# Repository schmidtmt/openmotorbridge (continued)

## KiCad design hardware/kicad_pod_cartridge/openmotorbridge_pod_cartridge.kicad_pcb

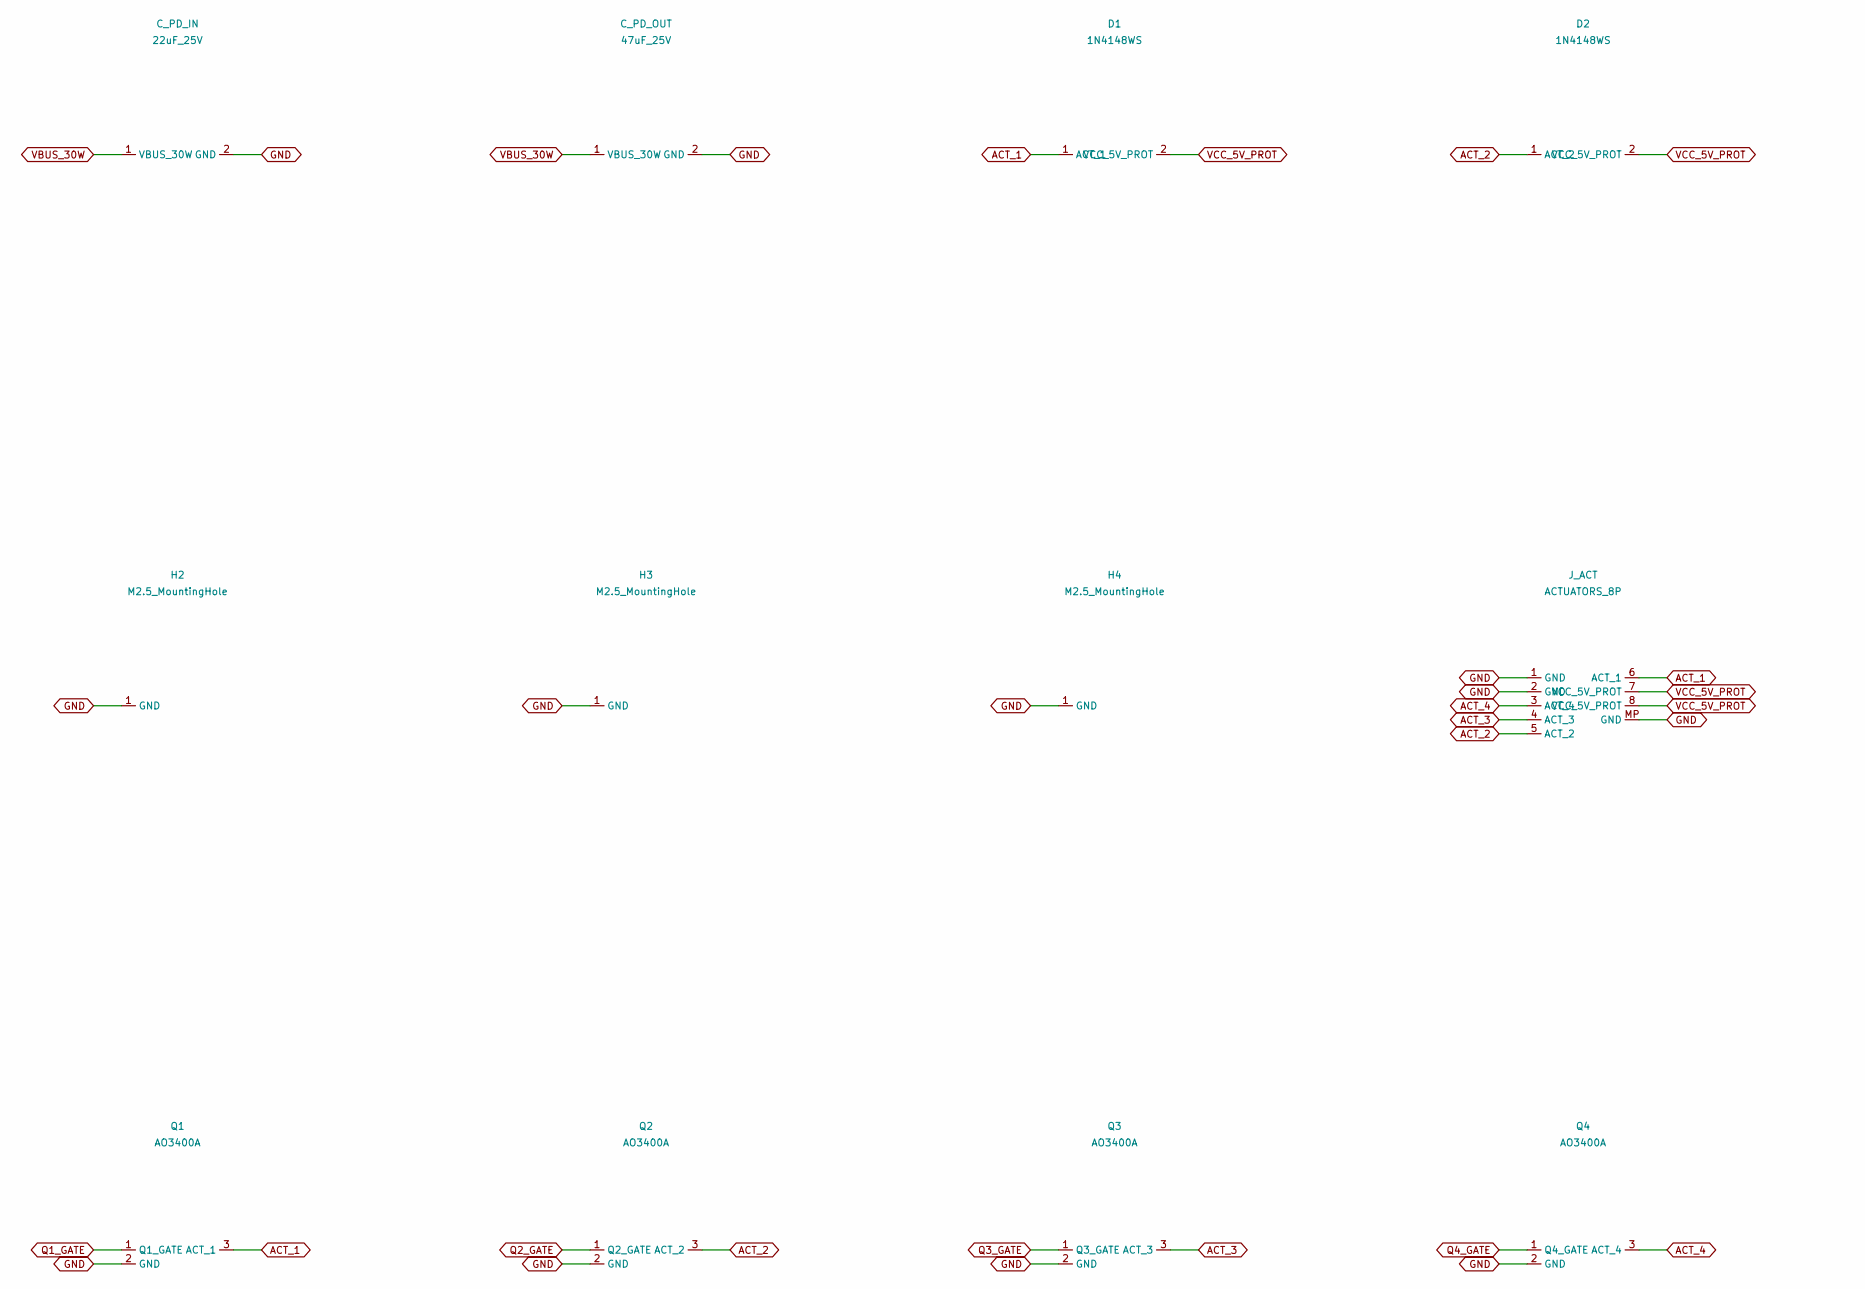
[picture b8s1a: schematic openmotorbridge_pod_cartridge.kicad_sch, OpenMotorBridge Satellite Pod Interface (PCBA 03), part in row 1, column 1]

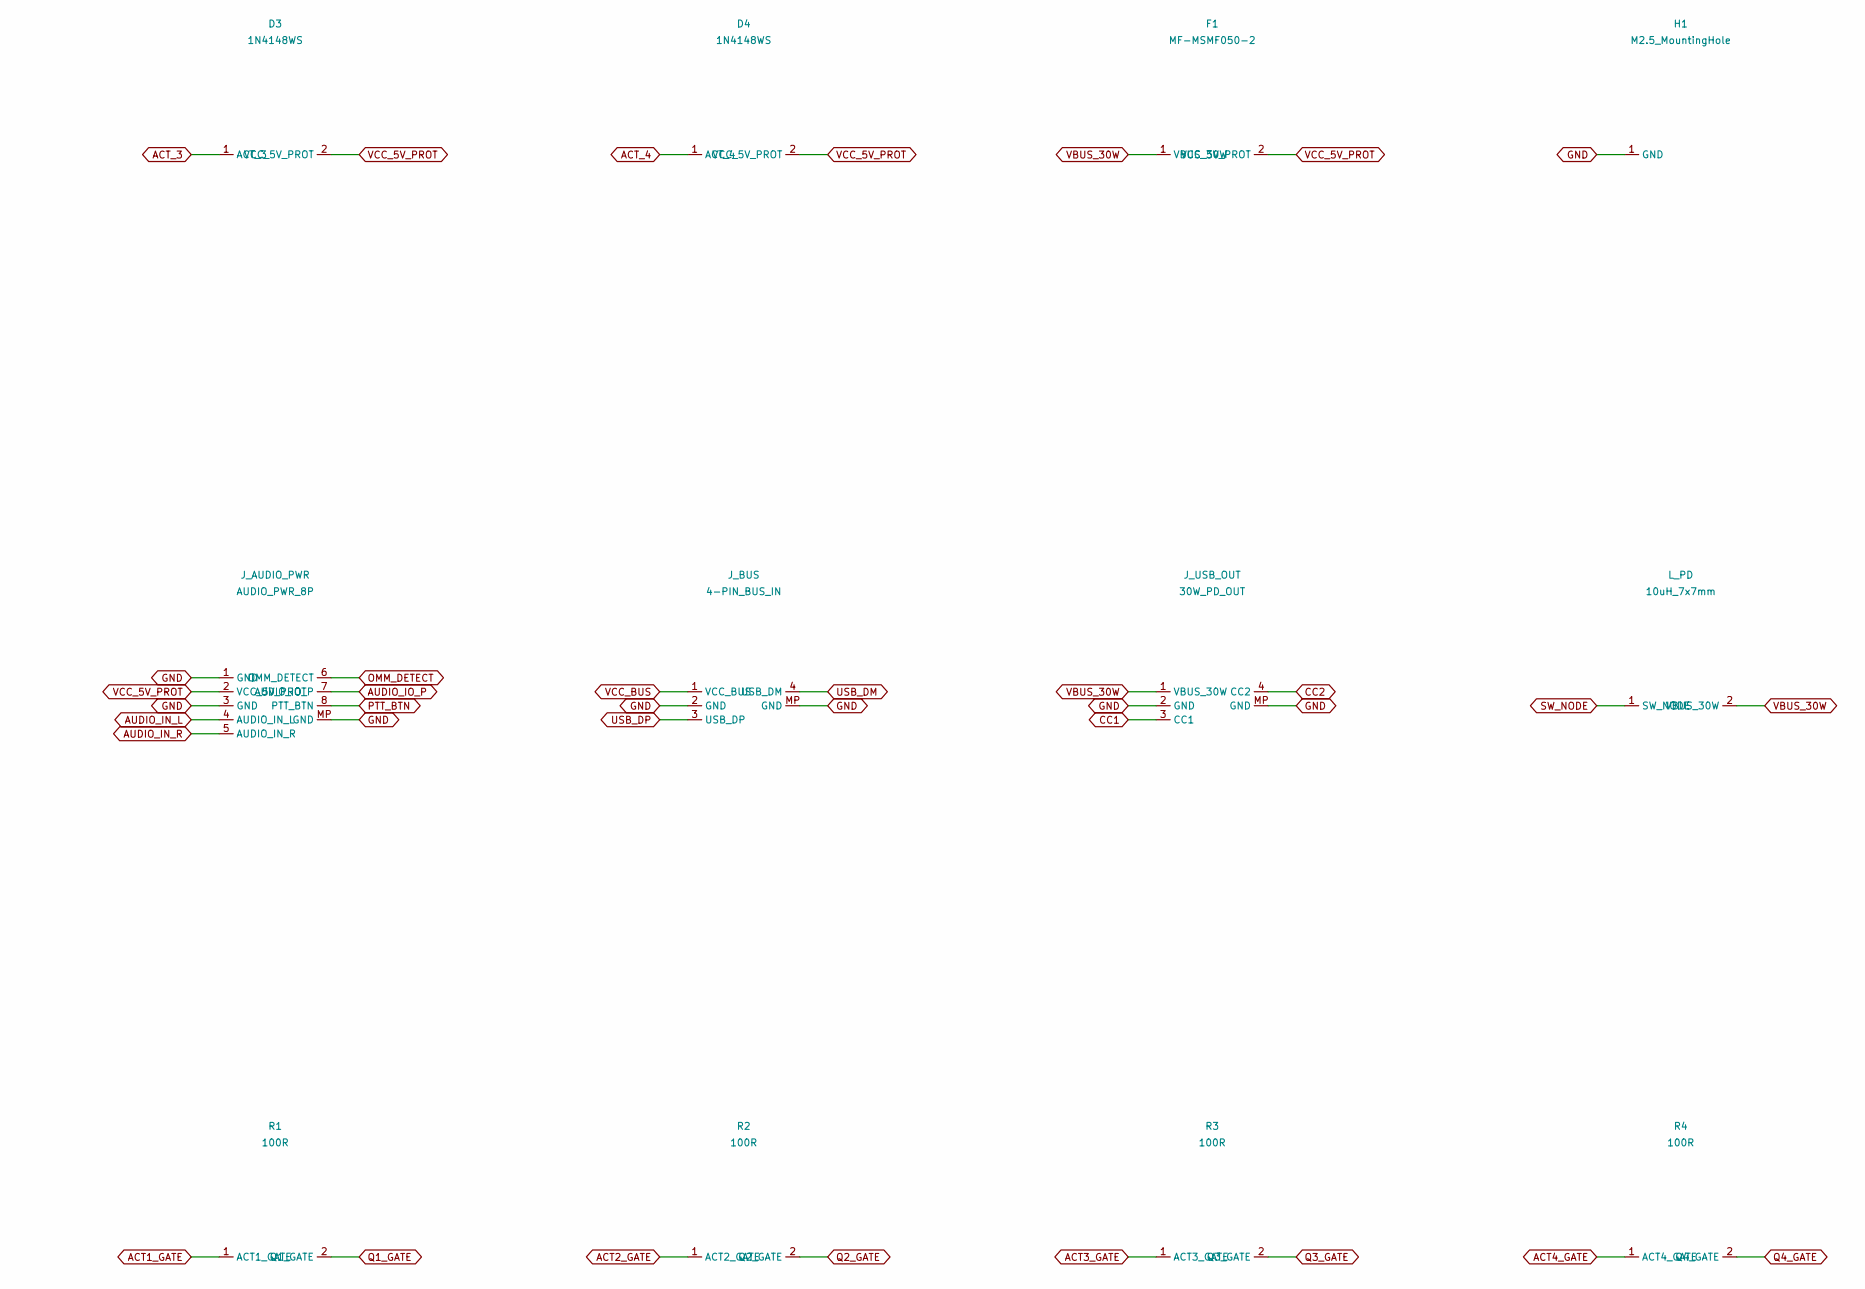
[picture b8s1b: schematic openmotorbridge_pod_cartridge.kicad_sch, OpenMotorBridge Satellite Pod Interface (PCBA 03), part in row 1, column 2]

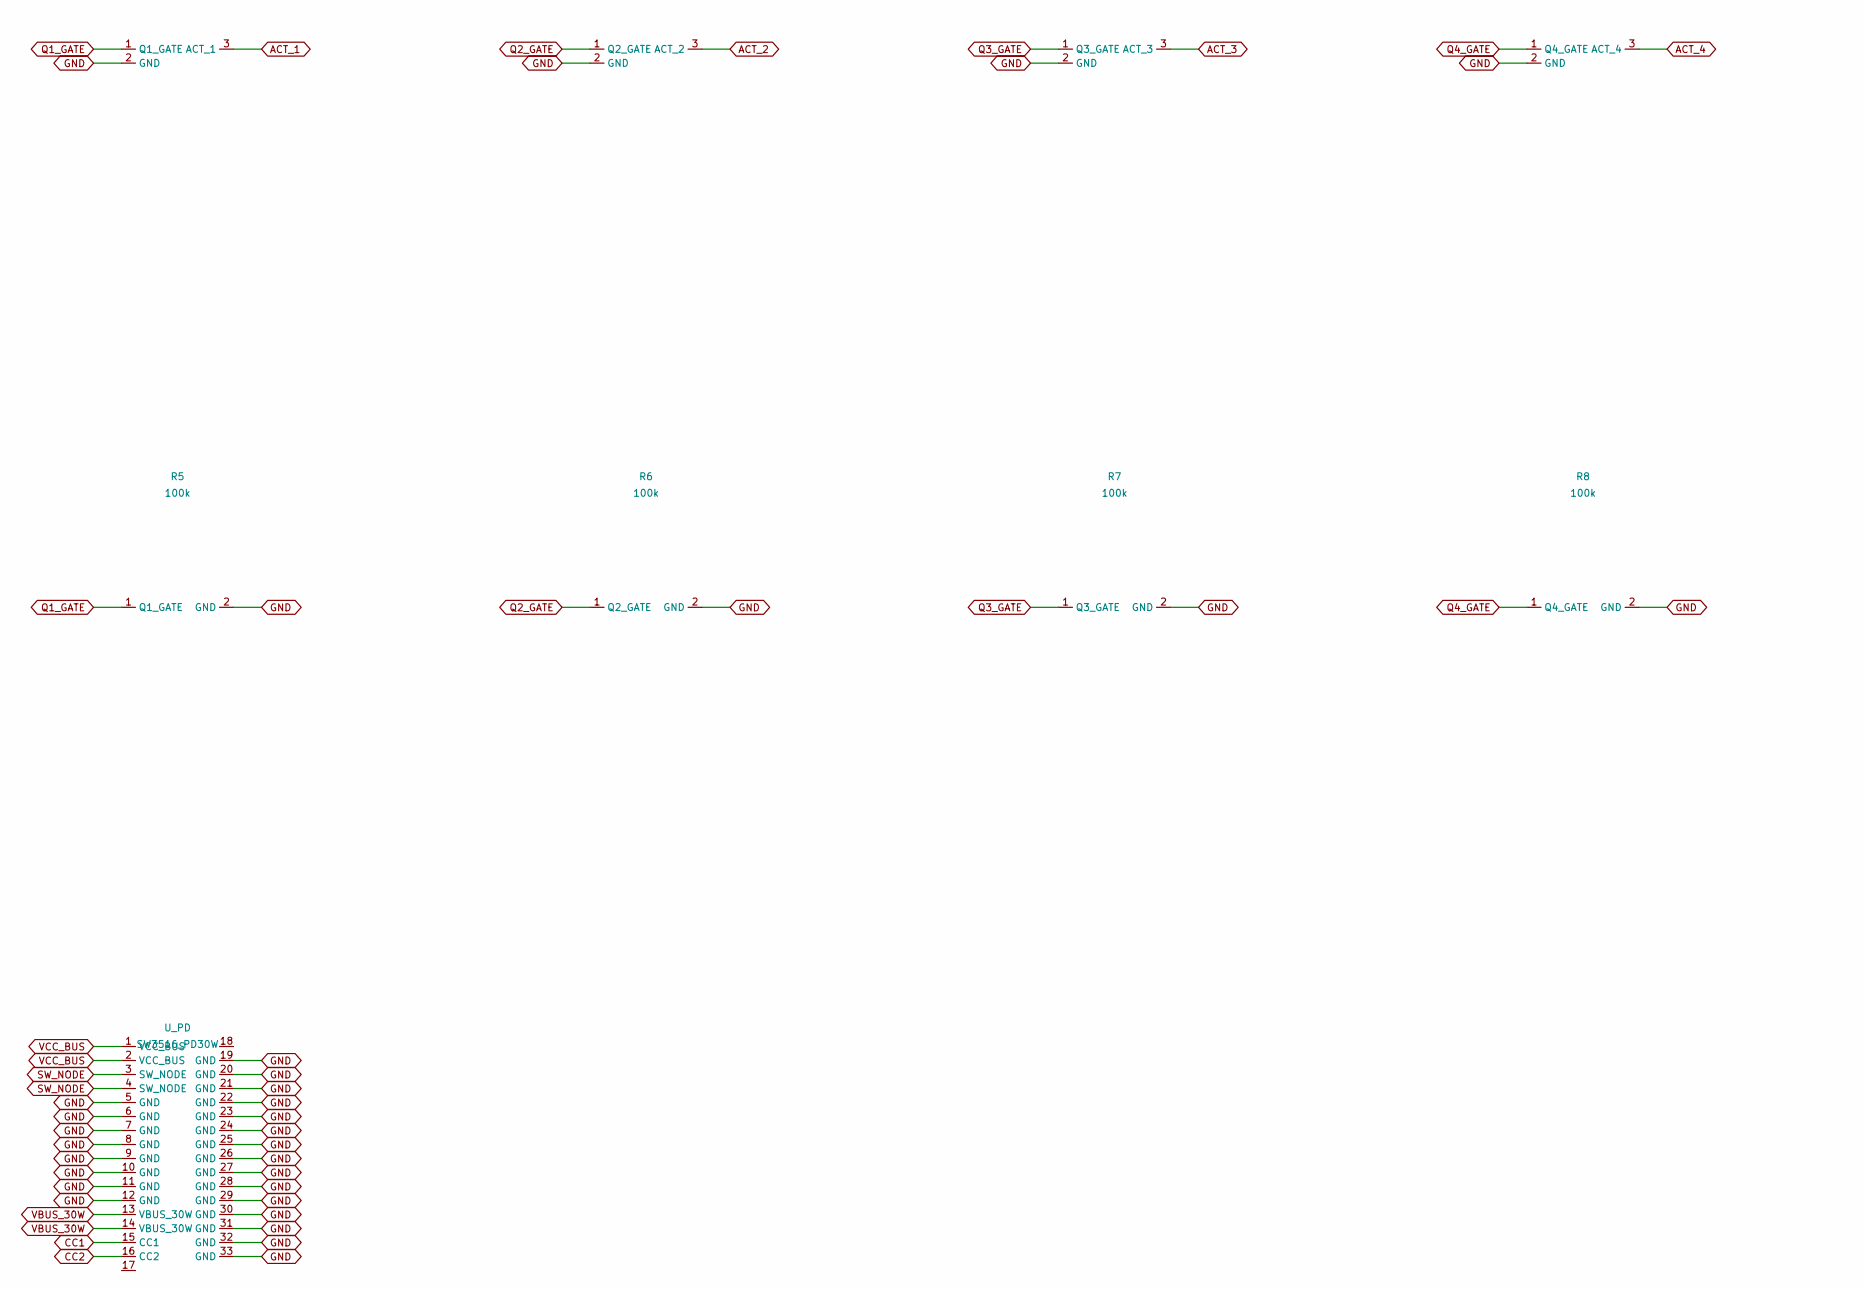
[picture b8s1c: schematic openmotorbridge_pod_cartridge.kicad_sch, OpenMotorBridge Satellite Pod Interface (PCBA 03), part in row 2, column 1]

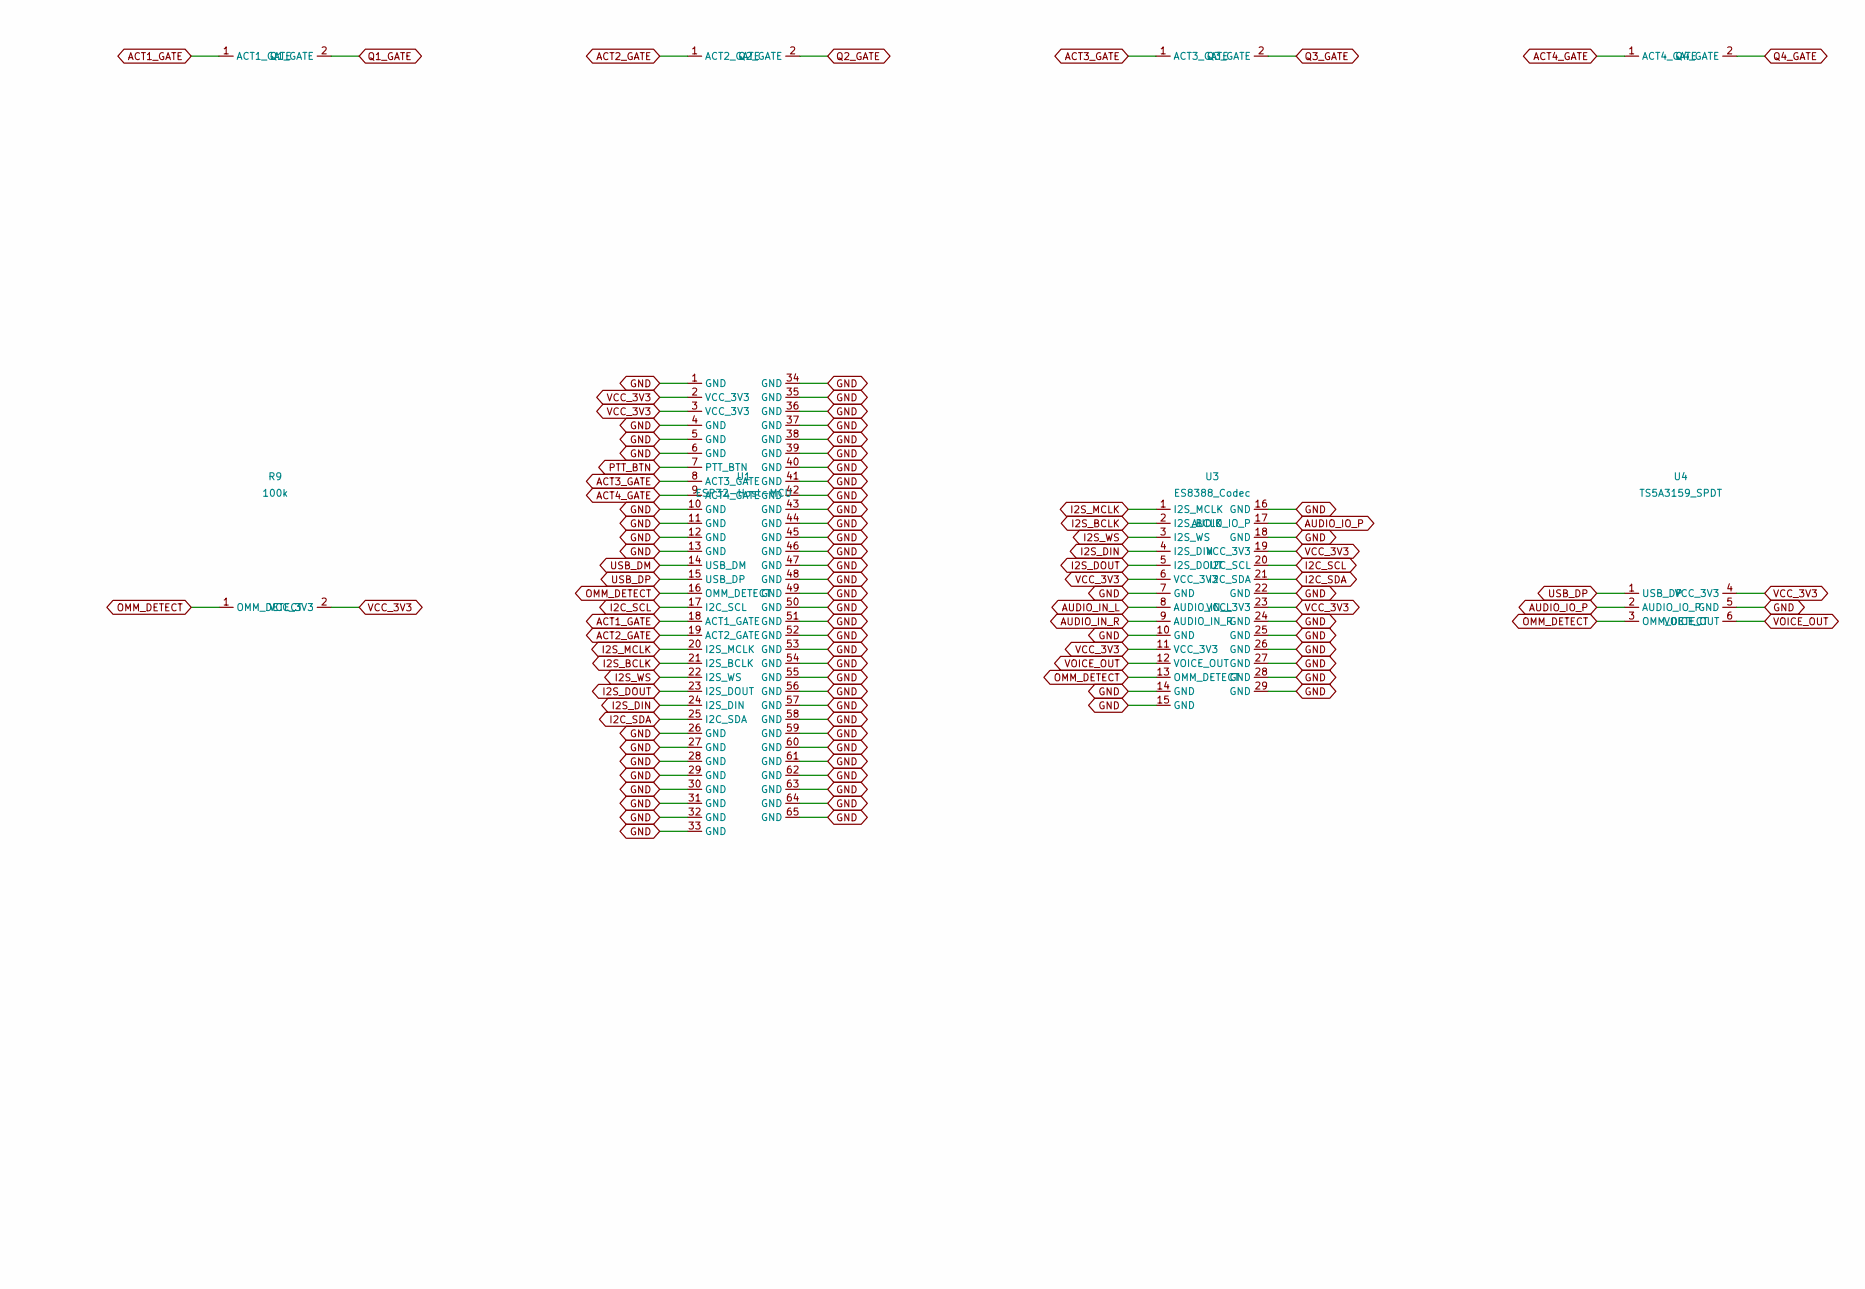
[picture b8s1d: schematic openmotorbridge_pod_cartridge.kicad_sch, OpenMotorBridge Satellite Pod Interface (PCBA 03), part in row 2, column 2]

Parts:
C_PD_IN: 22uF_25V; C_1210_3225Metric
C_PD_OUT: 47uF_25V; C_1210_3225Metric
D1, D2, D3, D4: 1N4148WS; D_SOD-323
F1: MF-MSMF050-2; Fuse_1812_4532Metric
H1, H2, H3, H4: M2.5_MountingHole; MountingHole_2.7mm_M2.5_Pad
J_ACT: ACTUATORS_8P; JST_SH_BM08B-SRSS-TB_1x08-1MP_P1.00mm_Vertical
J_AUDIO_PWR: AUDIO_PWR_8P; JST_SH_BM08B-SRSS-TB_1x08-1MP_P1.00mm_Vertical
J_BUS: 4-PIN_BUS_IN; JST_GH_BM04B-GHS-TBT_1x04-1MP_P1.25mm_Vertical
J_USB_OUT: 30W_PD_OUT; JST_GH_BM04B-GHS-TBT_1x04-1MP_P1.25mm_Vertical
L_PD: 10uH_7x7mm; L_Wuerth_WE-PD-Typ-7345
Q1, Q2, Q3, Q4: AO3400A; SOT-23
R1, R2, R3, R4: 100R; R_0603_1608Metric
R5, R6, R7, R8, R9: 100k; R_0603_1608Metric
U1: ESP32-Host-MCU; ESP32-C6-MINI-1
U3: ES8388_Codec; QFN-28-1EP_4x4mm_P0.4mm_EP2.4x2.4mm
U4: TS5A3159_SPDT; SOT-23-6
U_PD: SW3516_PD30W; QFN-32-1EP_5x5mm_P0.5mm_EP3.45x3.45mm_ThermalVias

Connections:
ACT1_GATE: R1.1 (ACT1_GATE), U1.18 (ACT1_GATE)
ACT2_GATE: R2.1 (ACT2_GATE), U1.19 (ACT2_GATE)
ACT3_GATE: R3.1 (ACT3_GATE), U1.8 (ACT3_GATE)
ACT4_GATE: R4.1 (ACT4_GATE), U1.9 (ACT4_GATE)
ACT_1: D1.1 (ACT_1), J_ACT.6 (ACT_1), Q1.3 (ACT_1)
ACT_2: D2.1 (ACT_2), J_ACT.5 (ACT_2), Q2.3 (ACT_2)
ACT_3: D3.1 (ACT_3), J_ACT.4 (ACT_3), Q3.3 (ACT_3)
ACT_4: D4.1 (ACT_4), J_ACT.3 (ACT_4), Q4.3 (ACT_4)
AUDIO_IN_L: J_AUDIO_PWR.4 (AUDIO_IN_L), U3.8 (AUDIO_IN_L)
AUDIO_IN_R: J_AUDIO_PWR.5 (AUDIO_IN_R), U3.9 (AUDIO_IN_R)
AUDIO_IO_P: J_AUDIO_PWR.7 (AUDIO_IO_P), U3.17 (AUDIO_IO_P), U4.2 (AUDIO_IO_P)
CC1: J_USB_OUT.3 (CC1), U_PD.15 (CC1)
CC2: J_USB_OUT.4 (CC2), U_PD.16 (CC2)
GND: C_PD_IN.2 (GND), C_PD_OUT.2 (GND), H1.1, H2.1, H3.1, H4.1, J_ACT.1 (GND), J_ACT.2 (GND), J_ACT.MP (GND), J_AUDIO_PWR.1 (GND), J_AUDIO_PWR.3 (GND), J_AUDIO_PWR.MP (GND), J_BUS.2 (GND), J_BUS.MP (GND), J_USB_OUT.2 (GND), J_USB_OUT.MP (GND), Q1.2 (GND), Q2.2 (GND), Q3.2 (GND), Q4.2 (GND), R5.2 (GND), R6.2 (GND), R7.2 (GND), R8.2 (GND), U1.1 (GND), U1.4 (GND), U1.5 (GND), U1.6 (GND), U1.10 (GND), U1.11 (GND), U1.12 (GND), U1.13 (GND), U1.26 (GND), U1.27 (GND), U1.28 (GND), U1.29 (GND), U1.30 (GND), U1.31 (GND), U1.32 (GND), U1.33 (GND), U1.34 (GND), U1.35 (GND), U1.36 (GND), U1.37 (GND), U1.38 (GND), U1.39 (GND), U1.40 (GND), U1.41 (GND), U1.42 (GND), U1.43 (GND), U1.44 (GND), U1.45 (GND), U1.46 (GND), U1.47 (GND), U1.48 (GND), U1.49 (GND), U1.50 (GND), U1.51 (GND), U1.52 (GND), U1.53 (GND), U1.54 (GND), U1.55 (GND), U1.56 (GND), U1.57 (GND), U1.58 (GND), U1.59 (GND), U1.60 (GND), U1.61 (GND), U1.62 (GND), U1.63 (GND), U1.64 (GND), U1.65 (GND), U3.7 (GND), U3.10 (GND), U3.14 (GND), U3.15 (GND), U3.16 (GND), U3.18 (GND), U3.22 (GND), U3.24 (GND), U3.25 (GND), U3.26 (GND), U3.27 (GND), U3.28 (GND), U3.29 (GND), U4.5 (GND), U_PD.5 (GND), U_PD.6 (GND), U_PD.7 (GND), U_PD.8 (GND), U_PD.9 (GND), U_PD.10 (GND), U_PD.11 (GND), U_PD.12 (GND), U_PD.19 (GND), U_PD.20 (GND), U_PD.21 (GND), U_PD.22 (GND), U_PD.23 (GND), U_PD.24 (GND), U_PD.25 (GND), U_PD.26 (GND), U_PD.27 (GND), U_PD.28 (GND), U_PD.29 (GND), U_PD.30 (GND), U_PD.31 (GND), U_PD.32 (GND), U_PD.33 (GND)
I2C_SCL: U1.17 (I2C_SCL), U3.20 (I2C_SCL)
I2C_SDA: U1.25 (I2C_SDA), U3.21 (I2C_SDA)
I2S_BCLK: U1.21 (I2S_BCLK), U3.2 (I2S_BCLK)
I2S_DIN: U1.24 (I2S_DIN), U3.4 (I2S_DIN)
I2S_DOUT: U1.23 (I2S_DOUT), U3.5 (I2S_DOUT)
I2S_MCLK: U1.20 (I2S_MCLK), U3.1 (I2S_MCLK)
I2S_WS: U1.22 (I2S_WS), U3.3 (I2S_WS)
OMM_DETECT: J_AUDIO_PWR.6 (OMM_DETECT), R9.1 (OMM_DETECT), U1.16 (OMM_DETECT), U3.13 (OMM_DETECT), U4.3 (OMM_DETECT)
PTT_BTN: J_AUDIO_PWR.8 (PTT_BTN), U1.7 (PTT_BTN)
Q1_GATE: Q1.1 (Q1_GATE), R1.2 (Q1_GATE), R5.1 (Q1_GATE)
Q2_GATE: Q2.1 (Q2_GATE), R2.2 (Q2_GATE), R6.1 (Q2_GATE)
Q3_GATE: Q3.1 (Q3_GATE), R3.2 (Q3_GATE), R7.1 (Q3_GATE)
Q4_GATE: Q4.1 (Q4_GATE), R4.2 (Q4_GATE), R8.1 (Q4_GATE)
SW_NODE: L_PD.1 (SW_NODE), U_PD.3 (SW_NODE), U_PD.4 (SW_NODE)
USB_DM: J_BUS.4 (USB_DM), U1.14 (USB_DM)
USB_DP: J_BUS.3 (USB_DP), U1.15 (USB_DP), U4.1 (USB_DP)
VBUS_30W: C_PD_IN.1 (VBUS_30W), C_PD_OUT.1 (VBUS_30W), F1.1 (VBUS_30W), J_USB_OUT.1 (VBUS_30W), L_PD.2 (VBUS_30W), U_PD.13 (VBUS_30W), U_PD.14 (VBUS_30W)
VCC_3V3: R9.2 (VCC_3V3), U1.2 (VCC_3V3), U1.3 (VCC_3V3), U3.6 (VCC_3V3), U3.11 (VCC_3V3), U3.19 (VCC_3V3), U3.23 (VCC_3V3), U4.4 (VCC_3V3)
VCC_5V_PROT: D1.2 (VCC_5V_PROT), D2.2 (VCC_5V_PROT), D3.2 (VCC_5V_PROT), D4.2 (VCC_5V_PROT), F1.2 (VCC_5V_PROT), J_ACT.7 (VCC_5V_PROT), J_ACT.8 (VCC_5V_PROT), J_AUDIO_PWR.2 (VCC_5V_PROT)
VCC_BUS: J_BUS.1 (VCC_BUS), U_PD.1 (VCC_BUS), U_PD.2 (VCC_BUS)
VOICE_OUT: U3.12 (VOICE_OUT), U4.6 (VOICE_OUT)

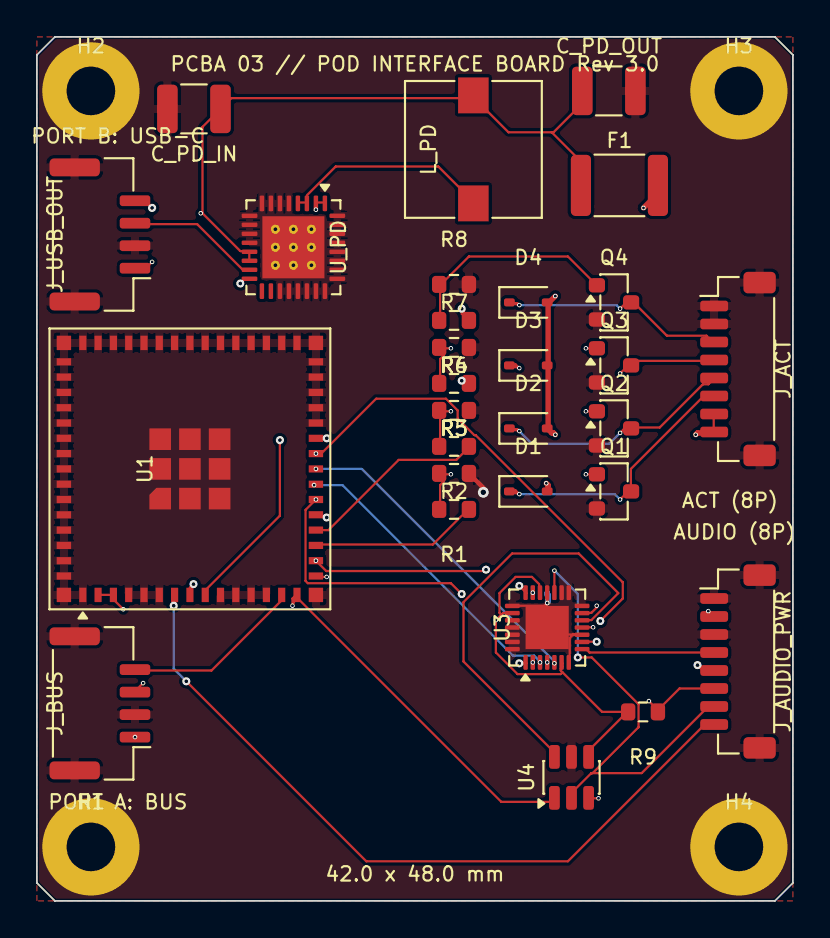
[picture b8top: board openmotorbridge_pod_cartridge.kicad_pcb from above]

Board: 4 copper layers, 42.0 x 48.0 mm, 33 parts (0 on the bottom side), 35 nets.

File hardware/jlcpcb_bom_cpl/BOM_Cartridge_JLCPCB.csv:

Designator,Comment,Footprint,LCSC Part #,Quantity
C1,100nF,Capacitor_SMD:C_0603_1608Metric,,1
C2,10uF,Capacitor_SMD:C_0805_2012Metric,,1
"D1, D2, D3, D4",1N4148WS,Diode_SMD:D_SOD-323,,4
F1,MF-MSMF050-2,Fuse:Fuse_1812_4532Metric,,1
"H1, H2, H3, H4",M2_MountingHole,MountingHole:MountingHole_2.2mm_M2_Pad,,4
J1,POD_BASE_DOCKING_SOCKET_6P,Connector_PinSocket_2.54mm:PinSocket_1x06_P2.54mm_Horizontal,,1
J2,INTERCOM_HEADSET_6P,Connector_JST:JST_SH_SM06B-SRSS-TB_1x06-1MP_P1.00mm_Horizontal,,1
J_ACT,ACTUATORS_8P,Connector_JST:JST_SH_SM08B-SRSS-TB_1x08-1MP_P1.00mm_Horizontal,,1
"Q1, Q2, Q3, Q4",AO3400A,Package_TO_SOT_SMD:SOT-23,,4
"R1, R2, R3, R4",100R,Resistor_SMD:R_0603_1608Metric,,4
"R5, R6, R7, R8",100k,Resistor_SMD:R_0603_1608Metric,,4
R9,4.7k,Resistor_SMD:R_0603_1608Metric,,1
U1,CH32V003F4P6,Package_SO:TSSOP-20_4.4x6.5mm_P0.65mm,,1
